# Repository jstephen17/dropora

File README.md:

# dropora
An automated system designed to securely receive and store parcels when you are away.

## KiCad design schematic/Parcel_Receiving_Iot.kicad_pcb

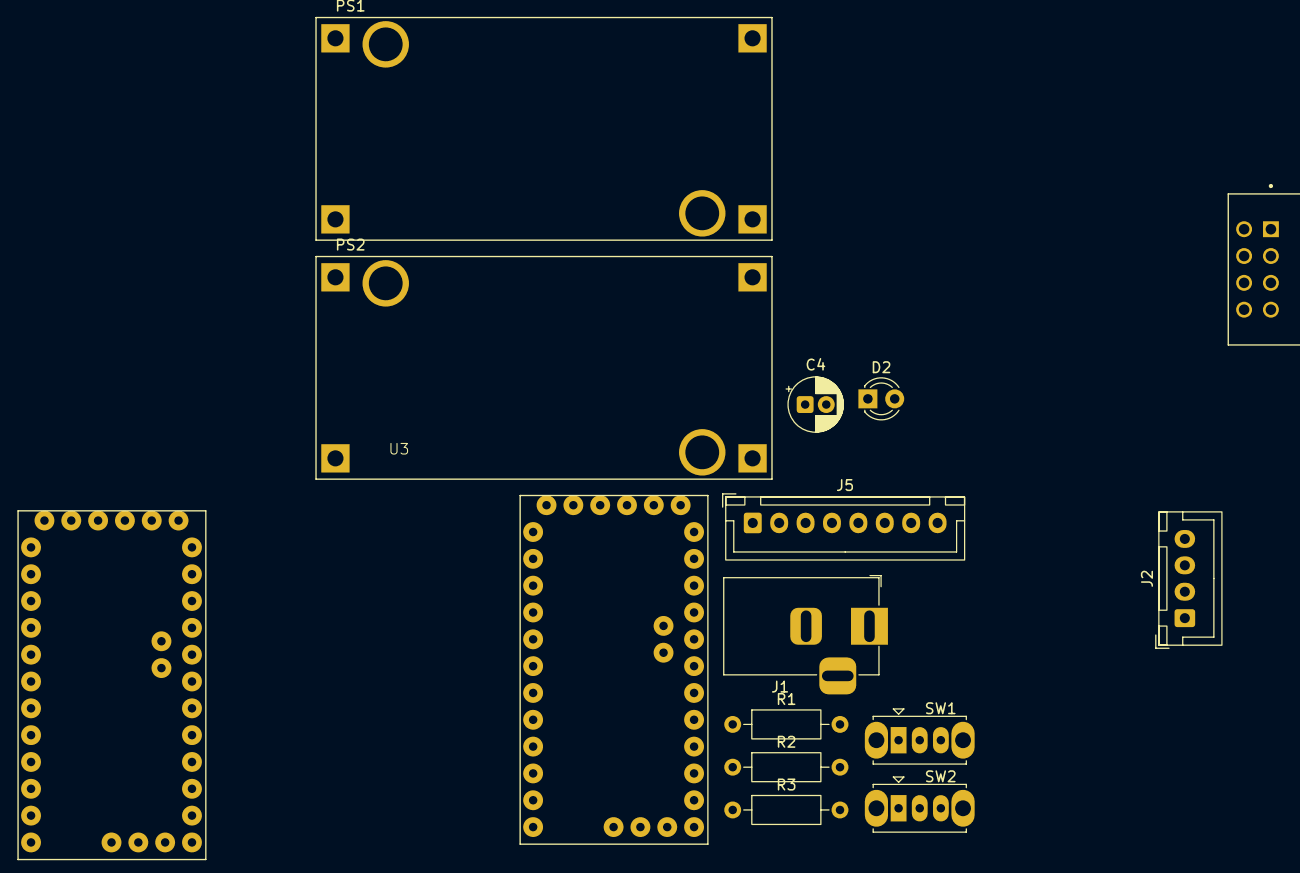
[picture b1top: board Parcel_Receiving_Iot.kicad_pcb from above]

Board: 2 copper layers, 15 parts (0 on the bottom side), 22 nets, no tracks yet.

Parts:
C4: C_Polarized; CP_Radial_D5.0mm_P2.00mm
D2: LED; LED_D3.0mm
J1: Barrel_Jack; BarrelJack_Horizontal
J2: Conn_01x04_Pin; JST_XH_B4B-XH-A_1x04_P2.50mm_Vertical
J5: Conn_01x08_Pin; JST_XH_B8B-XH-A_1x08_P2.50mm_Vertical
PS1, PS2: MC00100; CONV_MC00100
R1: 10k; R_Axial_DIN0207_L6.3mm_D2.5mm_P10.16mm_Horizontal
R2: 1k; R_Axial_DIN0207_L6.3mm_D2.5mm_P10.16mm_Horizontal
R3: 2k; R_Axial_DIN0207_L6.3mm_D2.5mm_P10.16mm_Horizontal
SW1, SW2: SW_SPDT; SW_Slide_SPDT_Straight_CK_OS102011MS2Q
U1, U3: ARDUINO_PRO_MINI_REV; MODULE_ARDUINO_PRO_MINI_REV
U2: ESP-01; MODULE_ESP-01

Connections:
+12V: C4.1, J1.1, PS1.IN+, PS2.IN+
A0: J5.7, U1.A0
GND: C4.2, J1.2, J2.4, J5.6, PS1.IN-, PS1.OUT-, PS2.IN-, PS2.OUT-, R3.2, U1.GND, U1.GND_1, U1.GND_2, U2.1 (GND), U3.GND, U3.GND_1, U3.GND_2
MISO-D12: J5.4, U1.D12 (MISO-D12)
MOSI-D11: J5.3, U1.D11 (MOSI-D11)
unnamed: PS1.MH1 (MOUTING), PS1.MH2 (MOUTING)
unnamed: PS2.MH1 (MOUTING), PS2.MH2 (MOUTING)
unnamed: R1.2, U2.7 (CH_PD)
unnamed: R2.2, R3.1, U2.4 (RXD)
OUT_3.3V: J5.8, PS1.OUT+, R1.1, U2.5 (VCC), U2.6 (~RST)
OUT_5V: J2.3, U3.VCC
OUT_8V: PS2.OUT+, U1.RAW, U3.RAW
RX_COMM_IN: SW1.1 (A), U3.RXI
RX_COMM_OUT: SW2.2 (B), U1.RXI
RX_TO_01_TX: U1.RXI_2, U2.8 (TXD)
SCK-D13: J5.2, U1.D13 (SCK-D13)
SCL_A5: J2.1, U3.A5
SDA-D10: J5.1, U1.D10
SDA_A4: J2.2, U3.A4
TX_COMM_IN: SW2.1 (A), U3.TXO
TX_COMM_OUT: SW1.2 (B), U1.TXO
TX_TO_01_DIVIDER: R2.1, U1.TXO_2
